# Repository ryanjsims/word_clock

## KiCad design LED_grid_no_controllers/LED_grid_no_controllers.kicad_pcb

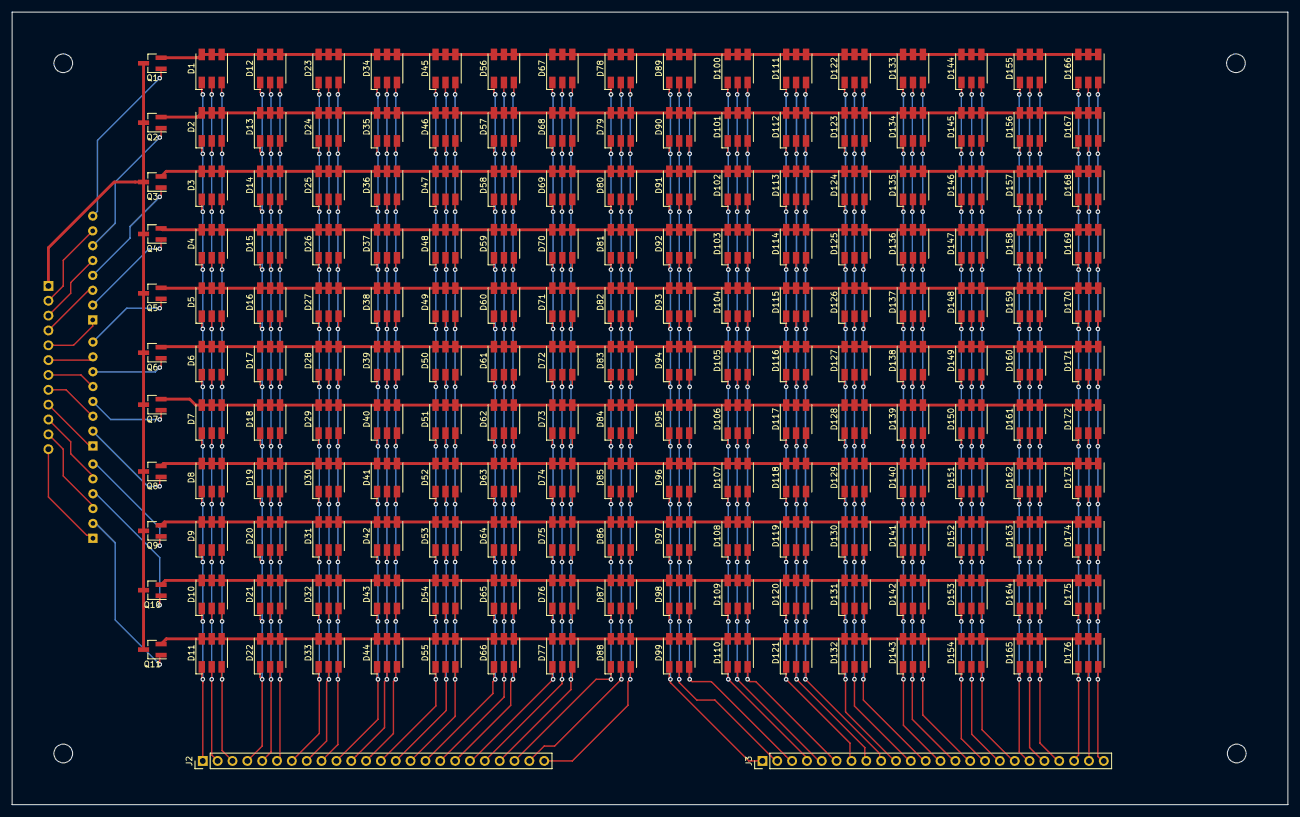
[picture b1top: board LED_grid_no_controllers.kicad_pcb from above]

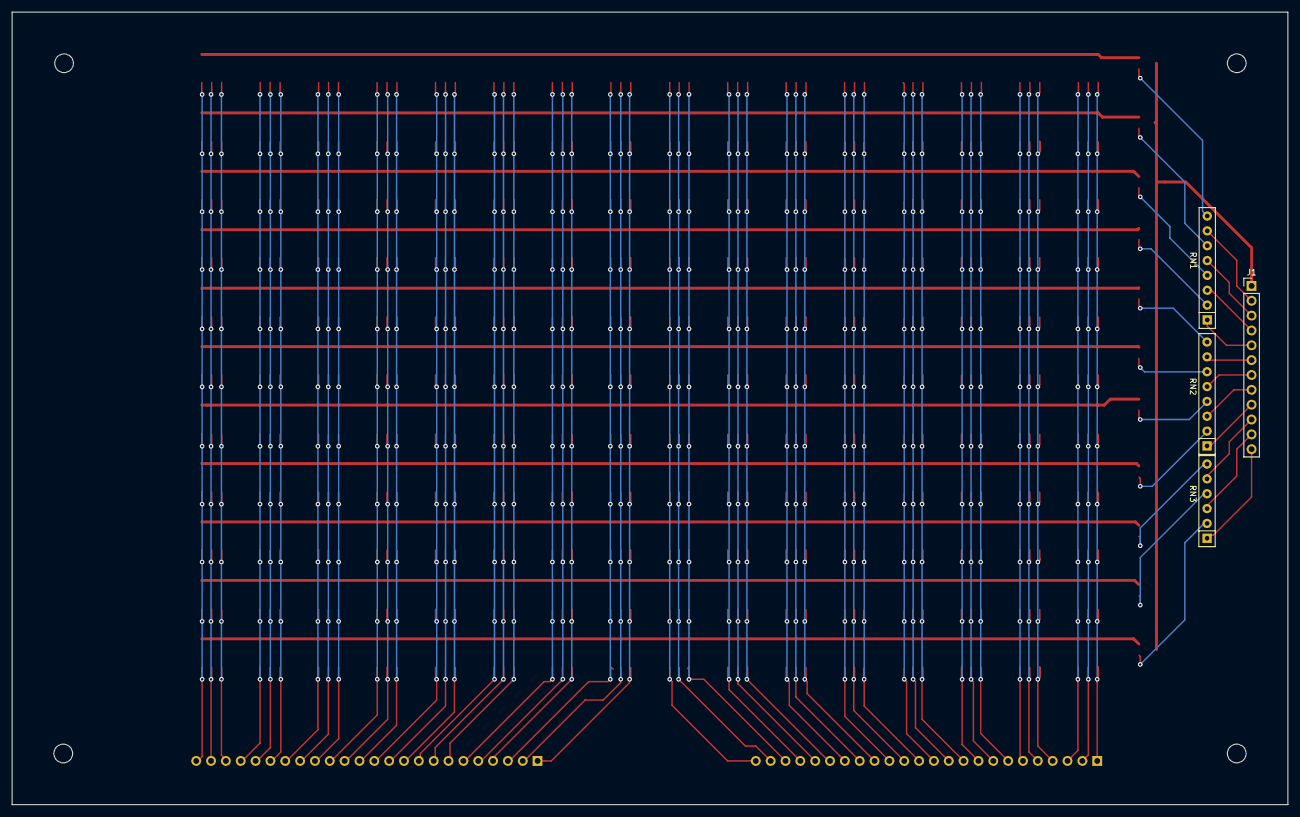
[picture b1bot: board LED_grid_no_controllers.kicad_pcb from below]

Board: 2 copper layers, 218.3 x 135.6 mm, 193 parts (4 on the bottom side), 82 nets.

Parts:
D1, D2, D3, D4, D5, D6, D7, D8, D9, D10, D11, D12, D13, D14, D15, D16, D17, D18, D19, D20, D21, D22, D23, D24, D25, D26, D27, D28, D29, D30, D31, D32, D33, D34, D35, D36, D37, D38, D39, D40, D41, D42, D43, D44, D45, D46, D47, D48, D49, D50, D51, D52, D53, D54, D55, D56, D57, D58, D59, D60, D61, D62, D63, D64, D65, D66, D67, D68, D69, D70, D71, D72, D73, D74, D75, D76, D77, D78, D79, D80, D81, D82, D83, D84, D85, D86, D87, D88, D89, D90, D91, D92, D93, D94, D95, D96, D97, D98, D99, D100, D101, D102, D103, D104, D105, D106, D107, D108, D109, D110, D111, D112, D113, D114, D115, D116, D117, D118, D119, D120, D121, D122, D123, D124, D125, D126, D127, D128, D129, D130, D131, D132, D133, D134, D135, D136, D137, D138, D139, D140, D141, D142, D143, D144, D145, D146, D147, D148, D149, D150, D151, D152, D153, D154, D155, D156, D157, D158, D159, D160, D161, D162, D163, D164, D165, D166, D167, D168, D169, D170, D171, D172, D173, D174, D175, D176: LED_RGB; LED_RGB_5050-6
J1: Conn_01x12; PinHeader_1x12_P2.54mm_Vertical
J2, J3: Conn_01x24; PinHeader_1x24_P2.54mm_Vertical
Q1, Q2, Q3, Q4, Q5, Q6, Q7, Q8, Q9, Q10, Q11: DNBT8105; SOT-23_Handsoldering
RN1, RN2: R_Pack04_SIP_10k; R_Array_SIP8
RN3: R_Pack03_SIP_10k; R_Array_SIP6

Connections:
+5V: J1.1, Q1.3, Q2.3, Q3.3, Q4.3, Q5.3, Q6.3, Q7.3, Q8.3, Q9.3, Q10.3, Q11.3
/B0: D1.3, D2.3, D3.3, D4.3, D5.3, D6.3, D7.3, D8.3, D9.3, D10.3, D11.3, J2.3
/B1: D12.3, D13.3, D14.3, D15.3, D16.3, D17.3, D18.3, D19.3, D20.3, D21.3, D22.3, J2.6
/B2: D23.3, D24.3, D25.3, D26.3, D27.3, D28.3, D29.3, D30.3, D31.3, D32.3, D33.3, J2.9
/B3: D34.3, D35.3, D36.3, D37.3, D38.3, D39.3, D40.3, D41.3, D42.3, D43.3, D44.3, J2.12
/B4: D45.3, D46.3, D47.3, D48.3, D49.3, D50.3, D51.3, D52.3, D53.3, D54.3, D55.3, J2.15
/B5: D56.3, D57.3, D58.3, D59.3, D60.3, D61.3, D62.3, D63.3, D64.3, D65.3, D66.3, J2.18
/B6: D67.3, D68.3, D69.3, D70.3, D71.3, D72.3, D73.3, D74.3, D75.3, D76.3, D77.3, J2.21
/B7: D78.3, D79.3, D80.3, D81.3, D82.3, D83.3, D84.3, D85.3, D86.3, D87.3, D88.3, J2.24
/B8: D89.3, D90.3, D91.3, D92.3, D93.3, D94.3, D95.3, D96.3, D97.3, D98.3, D99.3, J3.3
/B9: D100.3, D101.3, D102.3, D103.3, D104.3, D105.3, D106.3, D107.3, D108.3, D109.3, D110.3, J3.6
/B10: D111.3, D112.3, D113.3, D114.3, D115.3, D116.3, D117.3, D118.3, D119.3, D120.3, D121.3, J3.9
/B11: D122.3, D123.3, D124.3, D125.3, D126.3, D127.3, D128.3, D129.3, D130.3, D131.3, D132.3, J3.12
/B12: D133.3, D134.3, D135.3, D136.3, D137.3, D138.3, D139.3, D140.3, D141.3, D142.3, D143.3, J3.15
/B13: D144.3, D145.3, D146.3, D147.3, D148.3, D149.3, D150.3, D151.3, D152.3, D153.3, D154.3, J3.18
/B14: D155.3, D156.3, D157.3, D158.3, D159.3, D160.3, D161.3, D162.3, D163.3, D164.3, D165.3, J3.21
/B15: D166.3, D167.3, D168.3, D169.3, D170.3, D171.3, D172.3, D173.3, D174.3, D175.3, D176.3, J3.24
/G0: D1.2, D2.2, D3.2, D4.2, D5.2, D6.2, D7.2, D8.2, D9.2, D10.2, D11.2, J2.2
/G1: D12.2, D13.2, D14.2, D15.2, D16.2, D17.2, D18.2, D19.2, D20.2, D21.2, D22.2, J2.5
/G2: D23.2, D24.2, D25.2, D26.2, D27.2, D28.2, D29.2, D30.2, D31.2, D32.2, D33.2, J2.8
/G3: D34.2, D35.2, D36.2, D37.2, D38.2, D39.2, D40.2, D41.2, D42.2, D43.2, D44.2, J2.11
/G4: D45.2, D46.2, D47.2, D48.2, D49.2, D50.2, D51.2, D52.2, D53.2, D54.2, D55.2, J2.14
/G5: D56.2, D57.2, D58.2, D59.2, D60.2, D61.2, D62.2, D63.2, D64.2, D65.2, D66.2, J2.17
/G6: D67.2, D68.2, D69.2, D70.2, D71.2, D72.2, D73.2, D74.2, D75.2, D76.2, D77.2, J2.20
/G7: D78.2, D79.2, D80.2, D81.2, D82.2, D83.2, D84.2, D85.2, D86.2, D87.2, D88.2, J2.23
/G8: D89.2, D90.2, D91.2, D92.2, D93.2, D94.2, D95.2, D96.2, D97.2, D98.2, D99.2, J3.2
/G9: D100.2, D101.2, D102.2, D103.2, D104.2, D105.2, D106.2, D107.2, D108.2, D109.2, D110.2, J3.5
/G10: D111.2, D112.2, D113.2, D114.2, D115.2, D116.2, D117.2, D118.2, D119.2, D120.2, D121.2, J3.8
/G11: D122.2, D123.2, D124.2, D125.2, D126.2, D127.2, D128.2, D129.2, D130.2, D131.2, D132.2, J3.11
/G12: D133.2, D134.2, D135.2, D136.2, D137.2, D138.2, D139.2, D140.2, D141.2, D142.2, D143.2, J3.14
/G13: D144.2, D145.2, D146.2, D147.2, D148.2, D149.2, D150.2, D151.2, D152.2, D153.2, D154.2, J3.17
/G14: D155.2, D156.2, D157.2, D158.2, D159.2, D160.2, D161.2, D162.2, D163.2, D164.2, D165.2, J3.20
/G15: D166.2, D167.2, D168.2, D169.2, D170.2, D171.2, D172.2, D173.2, D174.2, D175.2, D176.2, J3.23
/R0: D1.1, D2.1, D3.1, D4.1, D5.1, D6.1, D7.1, D8.1, D9.1, D10.1, D11.1, J2.1
/R1: D12.1, D13.1, D14.1, D15.1, D16.1, D17.1, D18.1, D19.1, D20.1, D21.1, D22.1, J2.4
/R2: D23.1, D24.1, D25.1, D26.1, D27.1, D28.1, D29.1, D30.1, D31.1, D32.1, D33.1, J2.7
/R3: D34.1, D35.1, D36.1, D37.1, D38.1, D39.1, D40.1, D41.1, D42.1, D43.1, D44.1, J2.10
/R4: D45.1, D46.1, D47.1, D48.1, D49.1, D50.1, D51.1, D52.1, D53.1, D54.1, D55.1, J2.13
/R5: D56.1, D57.1, D58.1, D59.1, D60.1, D61.1, D62.1, D63.1, D64.1, D65.1, D66.1, J2.16
/R6: D67.1, D68.1, D69.1, D70.1, D71.1, D72.1, D73.1, D74.1, D75.1, D76.1, D77.1, J2.19
/R7: D78.1, D79.1, D80.1, D81.1, D82.1, D83.1, D84.1, D85.1, D86.1, D87.1, D88.1, J2.22
/R8: D89.1, D90.1, D91.1, D92.1, D93.1, D94.1, D95.1, D96.1, D97.1, D98.1, D99.1, J3.1
/R9: D100.1, D101.1, D102.1, D103.1, D104.1, D105.1, D106.1, D107.1, D108.1, D109.1, D110.1, J3.4
/R10: D111.1, D112.1, D113.1, D114.1, D115.1, D116.1, D117.1, D118.1, D119.1, D120.1, D121.1, J3.7
/R11: D122.1, D123.1, D124.1, D125.1, D126.1, D127.1, D128.1, D129.1, D130.1, D131.1, D132.1, J3.10
/R12: D133.1, D134.1, D135.1, D136.1, D137.1, D138.1, D139.1, D140.1, D141.1, D142.1, D143.1, J3.13
/R13: D144.1, D145.1, D146.1, D147.1, D148.1, D149.1, D150.1, D151.1, D152.1, D153.1, D154.1, J3.16
/R14: D155.1, D156.1, D157.1, D158.1, D159.1, D160.1, D161.1, D162.1, D163.1, D164.1, D165.1, J3.19
/R15: D166.1, D167.1, D168.1, D169.1, D170.1, D171.1, D172.1, D173.1, D174.1, D175.1, D176.1, J3.22
/ROW0: D1.4, D1.5, D1.6, D12.4, D12.5, D12.6, D23.4, D23.5, D23.6, D34.4, D34.5, D34.6, D45.4, D45.5, D45.6, D56.4, D56.5, D56.6, D67.4, D67.5, D67.6, D78.4, D78.5, D78.6, D89.4, D89.5, D89.6, D100.4, D100.5, D100.6, D111.4, D111.5, D111.6, D122.4, D122.5, D122.6, D133.4, D133.5, D133.6, D144.4, D144.5, D144.6, D155.4, D155.5, D155.6, D166.4, D166.5, D166.6, Q1.2
/ROW1: D2.4, D2.5, D2.6, D13.4, D13.5, D13.6, D24.4, D24.5, D24.6, D35.4, D35.5, D35.6, D46.4, D46.5, D46.6, D57.4, D57.5, D57.6, D68.4, D68.5, D68.6, D79.4, D79.5, D79.6, D90.4, D90.5, D90.6, D101.4, D101.5, D101.6, D112.4, D112.5, D112.6, D123.4, D123.5, D123.6, D134.4, D134.5, D134.6, D145.4, D145.5, D145.6, D156.4, D156.5, D156.6, D167.4, D167.5, D167.6, Q2.2
/ROW2: D3.4, D3.5, D3.6, D14.4, D14.5, D14.6, D25.4, D25.5, D25.6, D36.4, D36.5, D36.6, D47.4, D47.5, D47.6, D58.4, D58.5, D58.6, D69.4, D69.5, D69.6, D80.4, D80.5, D80.6, D91.4, D91.5, D91.6, D102.4, D102.5, D102.6, D113.4, D113.5, D113.6, D124.4, D124.5, D124.6, D135.4, D135.5, D135.6, D146.4, D146.5, D146.6, D157.4, D157.5, D157.6, D168.4, D168.5, D168.6, Q3.2
/ROW3: D4.4, D4.5, D4.6, D15.4, D15.5, D15.6, D26.4, D26.5, D26.6, D37.4, D37.5, D37.6, D48.4, D48.5, D48.6, D59.4, D59.5, D59.6, D70.4, D70.5, D70.6, D81.4, D81.5, D81.6, D92.4, D92.5, D92.6, D103.4, D103.5, D103.6, D114.4, D114.5, D114.6, D125.4, D125.5, D125.6, D136.4, D136.5, D136.6, D147.4, D147.5, D147.6, D158.4, D158.5, D158.6, D169.4, D169.5, D169.6, Q4.2
/ROW4: D5.4, D5.5, D5.6, D16.4, D16.5, D16.6, D27.4, D27.5, D27.6, D38.4, D38.5, D38.6, D49.4, D49.5, D49.6, D60.4, D60.5, D60.6, D71.4, D71.5, D71.6, D82.4, D82.5, D82.6, D93.4, D93.5, D93.6, D104.4, D104.5, D104.6, D115.4, D115.5, D115.6, D126.4, D126.5, D126.6, D137.4, D137.5, D137.6, D148.4, D148.5, D148.6, D159.4, D159.5, D159.6, D170.4, D170.5, D170.6, Q5.2
/ROW5: D6.4, D6.5, D6.6, D17.4, D17.5, D17.6, D28.4, D28.5, D28.6, D39.4, D39.5, D39.6, D50.4, D50.5, D50.6, D61.4, D61.5, D61.6, D72.4, D72.5, D72.6, D83.4, D83.5, D83.6, D94.4, D94.5, D94.6, D105.4, D105.5, D105.6, D116.4, D116.5, D116.6, D127.4, D127.5, D127.6, D138.4, D138.5, D138.6, D149.4, D149.5, D149.6, D160.4, D160.5, D160.6, D171.4, D171.5, D171.6, Q6.2
/ROW6: D7.4, D7.5, D7.6, D18.4, D18.5, D18.6, D29.4, D29.5, D29.6, D40.4, D40.5, D40.6, D51.4, D51.5, D51.6, D62.4, D62.5, D62.6, D73.4, D73.5, D73.6, D84.4, D84.5, D84.6, D95.4, D95.5, D95.6, D106.4, D106.5, D106.6, D117.4, D117.5, D117.6, D128.4, D128.5, D128.6, D139.4, D139.5, D139.6, D150.4, D150.5, D150.6, D161.4, D161.5, D161.6, D172.4, D172.5, D172.6, Q7.2
/ROW7: D8.4, D8.5, D8.6, D19.4, D19.5, D19.6, D30.4, D30.5, D30.6, D41.4, D41.5, D41.6, D52.4, D52.5, D52.6, D63.4, D63.5, D63.6, D74.4, D74.5, D74.6, D85.4, D85.5, D85.6, D96.4, D96.5, D96.6, D107.4, D107.5, D107.6, D118.4, D118.5, D118.6, D129.4, D129.5, D129.6, D140.4, D140.5, D140.6, D151.4, D151.5, D151.6, D162.4, D162.5, D162.6, D173.4, D173.5, D173.6, Q8.2
/ROW8: D9.4, D9.5, D9.6, D20.4, D20.5, D20.6, D31.4, D31.5, D31.6, D42.4, D42.5, D42.6, D53.4, D53.5, D53.6, D64.4, D64.5, D64.6, D75.4, D75.5, D75.6, D86.4, D86.5, D86.6, D97.4, D97.5, D97.6, D108.4, D108.5, D108.6, D119.4, D119.5, D119.6, D130.4, D130.5, D130.6, D141.4, D141.5, D141.6, D152.4, D152.5, D152.6, D163.4, D163.5, D163.6, D174.4, D174.5, D174.6, Q9.2
/ROW9: D10.4, D10.5, D10.6, D21.4, D21.5, D21.6, D32.4, D32.5, D32.6, D43.4, D43.5, D43.6, D54.4, D54.5, D54.6, D65.4, D65.5, D65.6, D76.4, D76.5, D76.6, D87.4, D87.5, D87.6, D98.4, D98.5, D98.6, D109.4, D109.5, D109.6, D120.4, D120.5, D120.6, D131.4, D131.5, D131.6, D142.4, D142.5, D142.6, D153.4, D153.5, D153.6, D164.4, D164.5, D164.6, D175.4, D175.5, D175.6, Q10.2
/ROW10: D11.4, D11.5, D11.6, D22.4, D22.5, D22.6, D33.4, D33.5, D33.6, D44.4, D44.5, D44.6, D55.4, D55.5, D55.6, D66.4, D66.5, D66.6, D77.4, D77.5, D77.6, D88.4, D88.5, D88.6, D99.4, D99.5, D99.6, D110.4, D110.5, D110.6, D121.4, D121.5, D121.6, D132.4, D132.5, D132.6, D143.4, D143.5, D143.6, D154.4, D154.5, D154.6, D165.4, D165.5, D165.6, D176.4, D176.5, D176.6, Q11.2
/ROW_IN_0: J1.2, RN1.7
/ROW_IN_1: J1.3, RN1.5
/ROW_IN_2: J1.4, RN1.3
/ROW_IN_3: J1.5, RN1.1
/ROW_IN_4: J1.6, RN2.7
/ROW_IN_5: J1.7, RN2.5
/ROW_IN_6: J1.8, RN2.3
/ROW_IN_7: J1.9, RN2.1
/ROW_IN_8: J1.10, RN3.5
/ROW_IN_9: J1.11, RN3.3
/ROW_IN_10: J1.12, RN3.1
/ROW_SEL_0: Q1.1, RN1.8
/ROW_SEL_1: Q2.1, RN1.6
/ROW_SEL_2: Q3.1, RN1.4
/ROW_SEL_3: Q4.1, RN1.2
/ROW_SEL_4: Q5.1, RN2.8
/ROW_SEL_5: Q6.1, RN2.6
/ROW_SEL_6: Q7.1, RN2.4
/ROW_SEL_7: Q8.1, RN2.2
/ROW_SEL_8: Q9.1, RN3.6
/ROW_SEL_9: Q10.1, RN3.4
/ROW_SEL_10: Q11.1, RN3.2

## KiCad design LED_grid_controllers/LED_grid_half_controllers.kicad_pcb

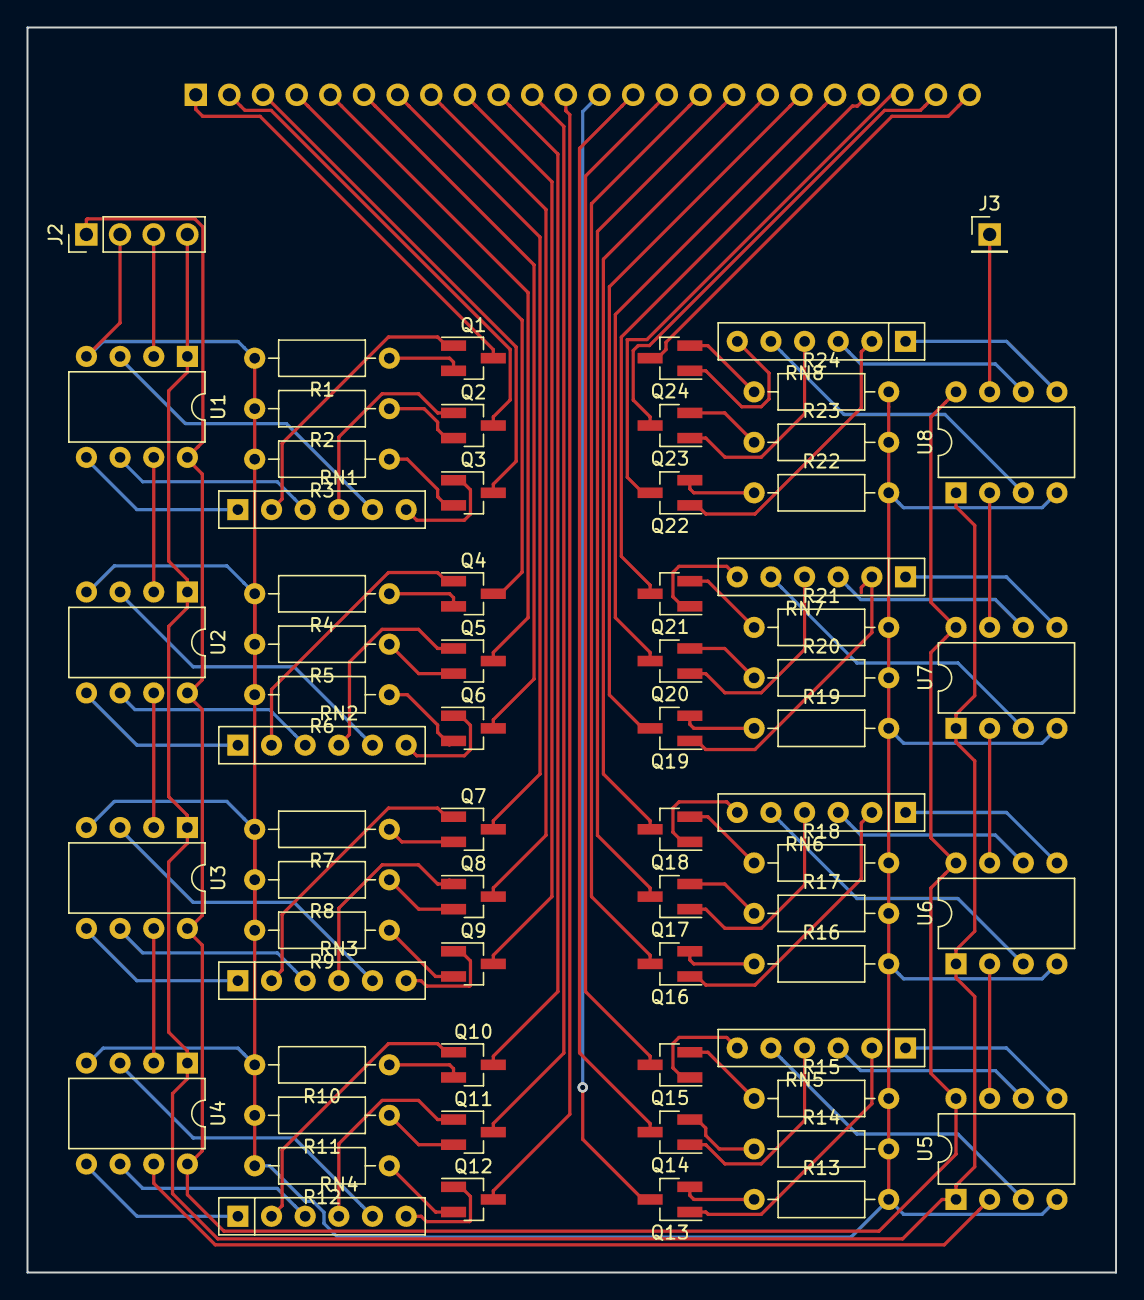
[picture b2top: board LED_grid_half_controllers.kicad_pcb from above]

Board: 2 copper layers, 82.2 x 94.0 mm, 67 parts (1 on the bottom side), 108 nets.

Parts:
J1: Conn_01x24; PinSocket_1x24_P2.54mm_Vertical
J2: Conn_01x04; PinHeader_1x04_P2.54mm_Vertical
J3: Conn_01x01; PinHeader_1x01_P2.54mm_Vertical
Q1, Q2, Q3, Q4, Q5, Q6, Q7, Q8, Q9, Q10, Q11, Q12, Q13, Q14, Q15, Q16, Q17, Q18, Q19, Q20, Q21, Q22, Q23, Q24: 2N3904_SOT-23; SOT-23_Handsoldering
R1, R4, R7, R10, R13, R16, R19, R22: 100; R_Axial_DIN0207_L6.3mm_D2.5mm_P10.16mm_Horizontal
R2, R3, R5, R6, R8, R9, R11, R12, R14, R15, R17, R18, R20, R21, R23, R24: 150; R_Axial_DIN0207_L6.3mm_D2.5mm_P10.16mm_Horizontal
RN1, RN2, RN3, RN4, RN5, RN6, RN7, RN8: R_Pack03_SIP_10k; R_Array_SIP6
U1, U2, U3, U4, U5, U6, U7, U8: ATtiny85-20PU; DIP-8_W7.62mm

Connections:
+5V: J2.1, U1.8, U2.8, U3.8, U4.8, U5.8, U6.8, U7.8, U8.8
/B0: J1.3, Q3.3
/B1: J1.6, Q6.3
/B2: J1.9, Q9.3
/B3: J1.12, Q12.3
/B4: J1.15, Q15.3
/B5: J1.18, Q18.3
/B6: J1.21, Q21.3
/B7: J1.24, Q24.3
/Controller0/B_PWM: RN1.5, U1.3
/Controller0/B_RES_OUT: Q3.1, RN1.6
/Controller0/G_PWM: RN1.3, U1.6
/Controller0/G_RES_OUT: Q2.1, RN1.4
/Controller0/R_PWM: RN1.1, U1.5
/Controller0/R_RES_OUT: Q1.1, RN1.2
/Controller1/B_PWM: RN2.5, U2.3
/Controller1/B_RES_OUT: Q6.1, RN2.6
/Controller1/DIN: U1.7, U2.2
/Controller1/G_PWM: RN2.3, U2.6
/Controller1/G_RES_OUT: Q5.1, RN2.4
/Controller1/R_PWM: RN2.1, U2.5
/Controller1/R_RES_OUT: Q4.1, RN2.2
/Controller2/B_PWM: RN3.5, U3.3
/Controller2/B_RES_OUT: Q9.1, RN3.6
/Controller2/DIN: U2.7, U3.2
/Controller2/G_PWM: RN3.3, U3.6
/Controller2/G_RES_OUT: Q8.1, RN3.4
/Controller2/R_PWM: RN3.1, U3.5
/Controller2/R_RES_OUT: Q7.1, RN3.2
/Controller3/B_PWM: RN4.5, U4.3
/Controller3/B_RES_OUT: Q12.1, RN4.6
/Controller3/DIN: U3.7, U4.2
/Controller3/G_PWM: RN4.3, U4.6
/Controller3/G_RES_OUT: Q11.1, RN4.4
/Controller3/R_PWM: RN4.1, U4.5
/Controller3/R_RES_OUT: Q10.1, RN4.2
/Controller4/B_PWM: RN5.5, U5.3
/Controller4/B_RES_OUT: Q15.1, RN5.6
/Controller4/G_PWM: RN5.3, U5.6
/Controller4/G_RES_OUT: Q14.1, RN5.4
/Controller4/R_PWM: RN5.1, U5.5
/Controller4/R_RES_OUT: Q13.1, RN5.2
/Controller5/B_PWM: RN6.5, U6.3
/Controller5/B_RES_OUT: Q18.1, RN6.6
/Controller5/DIN: U5.7, U6.2
/Controller5/G_PWM: RN6.3, U6.6
/Controller5/G_RES_OUT: Q17.1, RN6.4
/Controller5/R_PWM: RN6.1, U6.5
/Controller5/R_RES_OUT: Q16.1, RN6.2
/Controller6/B_PWM: RN7.5, U7.3
/Controller6/B_RES_OUT: Q21.1, RN7.6
/Controller6/DIN: U6.7, U7.2
/Controller6/G_PWM: RN7.3, U7.6
/Controller6/G_RES_OUT: Q20.1, RN7.4
/Controller6/R_PWM: RN7.1, U7.5
/Controller6/R_RES_OUT: Q19.1, RN7.2
/Controller7/B_PWM: RN8.5, U8.3
/Controller7/B_RES_OUT: Q24.1, RN8.6
/Controller7/DIN: U7.7, U8.2
/Controller7/G_PWM: RN8.3, U8.6
/Controller7/G_RES_OUT: Q23.1, RN8.4
/Controller7/R_PWM: RN8.1, U8.5
/Controller7/R_RES_OUT: Q22.1, RN8.2
/DCLK: J2.4, U1.1, U2.1, U3.1, U4.1, U5.1, U6.1, U7.1, U8.1
/DIN: J2.3, U1.2
/DOUT: J3.1, U8.7
/DOUT3: U4.7, U5.2
/G0: J1.2, Q2.3
/G1: J1.5, Q5.3
/G2: J1.8, Q8.3
/G3: J1.11, Q11.3
/G4: J1.14, Q14.3
/G5: J1.17, Q17.3
/G6: J1.20, Q20.3
/G7: J1.23, Q23.3
/R0: J1.1, Q1.3
/R1: J1.4, Q4.3
/R2: J1.7, Q7.3
/R3: J1.10, Q10.3
/R4: J1.13, Q13.3
/R5: J1.16, Q16.3
/R6: J1.19, Q19.3
/R7: J1.22, Q22.3
GND: J2.2, R1.2, R2.2, R3.2, R4.2, R5.2, R6.2, R7.2, R8.2, R9.2, R10.2, R11.2, R12.2, R13.2, R14.2, R15.2, R16.2, R17.2, R18.2, R19.2, R20.2, R21.2, R22.2, R23.2, R24.2, U1.4, U2.4, U3.4, U4.4, U5.4, U6.4, U7.4, U8.4
unnamed: Q1.2, R1.1
unnamed: Q2.2, R2.1
unnamed: Q3.2, R3.1
unnamed: Q4.2, R4.1
unnamed: Q5.2, R5.1
unnamed: Q6.2, R6.1
unnamed: Q7.2, R7.1
unnamed: Q8.2, R8.1
unnamed: Q9.2, R9.1
unnamed: Q10.2, R10.1
unnamed: Q11.2, R11.1
unnamed: Q12.2, R12.1
unnamed: Q13.2, R13.1
unnamed: Q14.2, R14.1
unnamed: Q15.2, R15.1
unnamed: Q16.2, R16.1
unnamed: Q17.2, R17.1
unnamed: Q18.2, R18.1
unnamed: Q19.2, R19.1
unnamed: Q20.2, R20.1
unnamed: Q21.2, R21.1
unnamed: Q22.2, R22.1
unnamed: Q23.2, R23.1
unnamed: Q24.2, R24.1

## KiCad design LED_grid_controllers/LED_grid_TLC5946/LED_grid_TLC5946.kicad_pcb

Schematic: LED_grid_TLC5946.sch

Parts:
C1, C2: 10pF; C_0805_2012Metric_Pad1.15x1.40mm_HandSolder
C3, C4, C5: 0.1uF; C_1206_3216Metric_Pad1.42x1.75mm_HandSolder
J1, J3: Conn_01x24; PinHeader_1x24_P2.54mm_Vertical
J2: Conn_01x10; PinHeader_1x10_P2.54mm_Vertical
R1, R2, R3: 3.3k; R_1206_3216Metric_Pad1.42x1.75mm_HandSolder
R4: >1MΩ; R_1206_3216Metric_Pad1.42x1.75mm_HandSolder
R5: 270Ω; R_1206_3216Metric_Pad1.42x1.75mm_HandSolder
U1, U2, U5: TLC5946PW; TSSOP-28_4.4x9.7mm_P0.65mm
U3: 74LVC1G08DBVR; SOT-23-5_HandSoldering
U4: 74LVC2G14DBVR; SOT-23-6_Handsoldering
Y1: 20MHz Crystal; Crystal_SMD_HC49-SD_HandSoldering

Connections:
/B0: J1.3, U1.9
/B1: J1.6, U1.12
/B2: J1.16, U1.15
/B3: J1.13, U1.18
/B4: J1.10, U1.21
/B5: J1.18, U2.8
/B6: J1.21, U2.11
/B7: J1.24, U2.14
/B8: J3.3, U2.17
/B9: J3.6, U2.20
/B10: J3.16, U5.7
/B11: J3.13, U5.10
/B12: J3.10, U5.13
/B13: J3.18, U5.16
/B14: J3.21, U5.19
/B15: J3.24, U5.22
/BLANK: J2.3, U1.2, U2.2, U5.2
/G0: J1.2, U1.8
/G1: J1.5, U1.11
/G2: J1.8, U1.14
/G3: J1.14, U1.17
/G4: J1.11, U1.20
/G5: J1.17, U2.7
/G6: J1.20, U2.10
/G7: J1.23, U2.13
/G8: J3.2, U2.16
/G9: J3.5, U2.19
/G10: J3.8, U2.22
/G11: J3.14, U5.9
/G12: J3.11, U5.12
/G13: J3.17, U5.15
/G14: J3.20, U5.18
/G15: J3.23, U5.21
/GSCLK: U1.25, U2.25, U3.4, U5.25
/GSCLK_EN: J2.8, U3.1
/MODE: J2.7, U1.6, U2.6, U5.6
/R0: J1.1, U1.7
/R1: J1.4, U1.10
/R2: J1.7, U1.13
/R3: J1.15, U1.16
/R4: J1.12, U1.19
/R5: J1.9, U1.22
/R6: J1.19, U2.9
/R7: J1.22, U2.12
/R8: J3.1, U2.15
/R9: J3.4, U2.18
/R10: J3.7, U2.21
/R11: J3.15, U5.8
/R12: J3.12, U5.11
/R13: J3.9, U5.14
/R14: J3.19, U5.17
/R15: J3.22, U5.20
/SCLK: J2.5, U1.4, U2.4, U5.4
/SIN: J2.6, U1.5
/SOUT0: U1.24, U2.5
/SOUT1: U2.24, U5.5
/SOUT2: J2.10, U5.24
/XERR: J2.9, U1.23, U2.23, U5.23
/XLAT: J2.4, U1.3, U2.3, U5.3
GND: C1.2, C2.2, C3.2, C4.2, C5.2, J2.2, R1.2, R2.2, R3.2, U1.1, U2.1, U3.3 (GND), U4.2, U5.1
unnamed: C1.1, R4.2, U4.1, Y1.1
unnamed: C2.1, R5.2, Y1.2
unnamed: R1.1, U1.27
unnamed: R2.1, U2.27
unnamed: R3.1, U5.27
unnamed: R4.1, R5.1, U4.3, U4.6
unnamed: U3.2, U4.4
VCC: C3.1, C4.1, C5.1, J2.1, U1.26, U1.28, U2.26, U2.28, U3.5 (VCC), U4.5, U5.26, U5.28

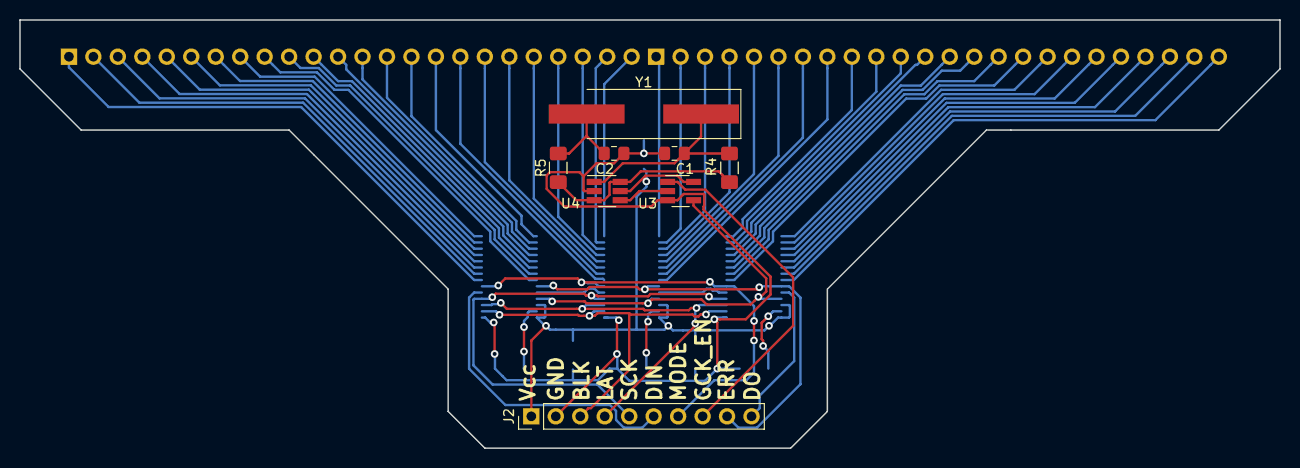
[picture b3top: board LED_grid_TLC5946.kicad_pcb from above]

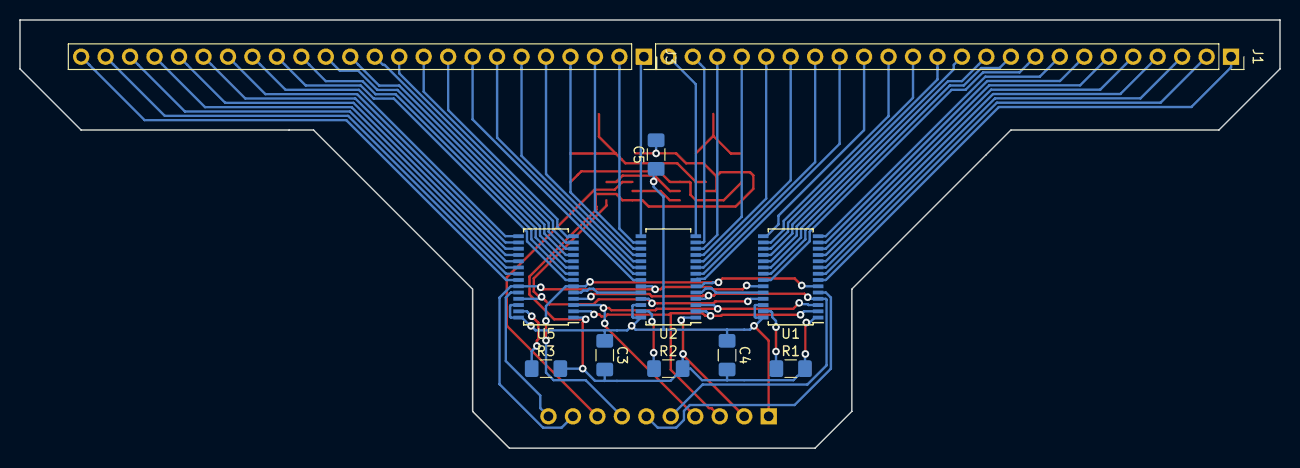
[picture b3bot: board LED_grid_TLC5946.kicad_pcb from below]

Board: 2 copper layers, 130.8 x 44.4 mm, 19 parts (11 on the bottom side), 68 nets.
